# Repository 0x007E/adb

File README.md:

# `ADB` - Analog Development Board

The `ADB` is a board with an [LM358](#additional-information) or any other 2-channel operational amplifier that meets the pin requirements. The board itself can be driven from `0 to 30V` or `+/-15V`. The board offers the possibility to create standard `OPA` circuits with `THT` resistors/capacitors and inductors or any other external circuit.

| Experience | Level |
|:------------|:-----:|
| Soldering   |  |

# Downloads

| Type      | File               | Description              |
|:---------:|:------------------:|:-------------------------|
| Schematic | [pdf](https://github.com/0x007E/adb/releases/latest/download/schematic.pdf) / [cadlab](https://cadlab.io/project/29896/main/files) | Schematic files |
| Board | [pdf](https://github.com/0x007E/adb/releases/latest/download/pcb.pdf) / [cadlab](https://cadlab.io/project/29896/main/files) | Board file |
| Drill | [pdf](https://github.com/0x007E/adb/releases/latest/download/drill.pdf) | Drill file |
| PCB | [zip](https://github.com/0x007E/adb/releases/latest/download/kicad.zip) / [tar](https://github.com/0x007E/adb/releases/latest/download/kicad.tar.gz) |  	KiCAD/Gerber/BoM/Drill files |
| Mechanical | [zip](https://github.com/0x007E/adb/releases/latest/download/freecad.zip) / [tar](https://github.com/0x007E/adb/releases/latest/download/freecad.tar.gz) | FreeCAD/Housing and exported step/stl files |

# Hardware

The pcb is created with `KiCAD`. All files are built with `github actions` so that they are ready for a production environment.

## PCB

The circuit board is populated on both sides (Top, Bottom). The best way for soldering the `SMD` components is within a vapor phase soldering system and for the `THT` components with a standard soldering system.

### Top Layer

### Bottom Layer

# Additional Information

| Type       | Link               | Description              |
|:----------:|:------------------:|:-------------------------|
| LM358 | [pdf](https://www.onsemi.com/download/data-sheet/pdf/lm358-d.pdf) | Dual operational amplifier |

---

R. GAECHTER

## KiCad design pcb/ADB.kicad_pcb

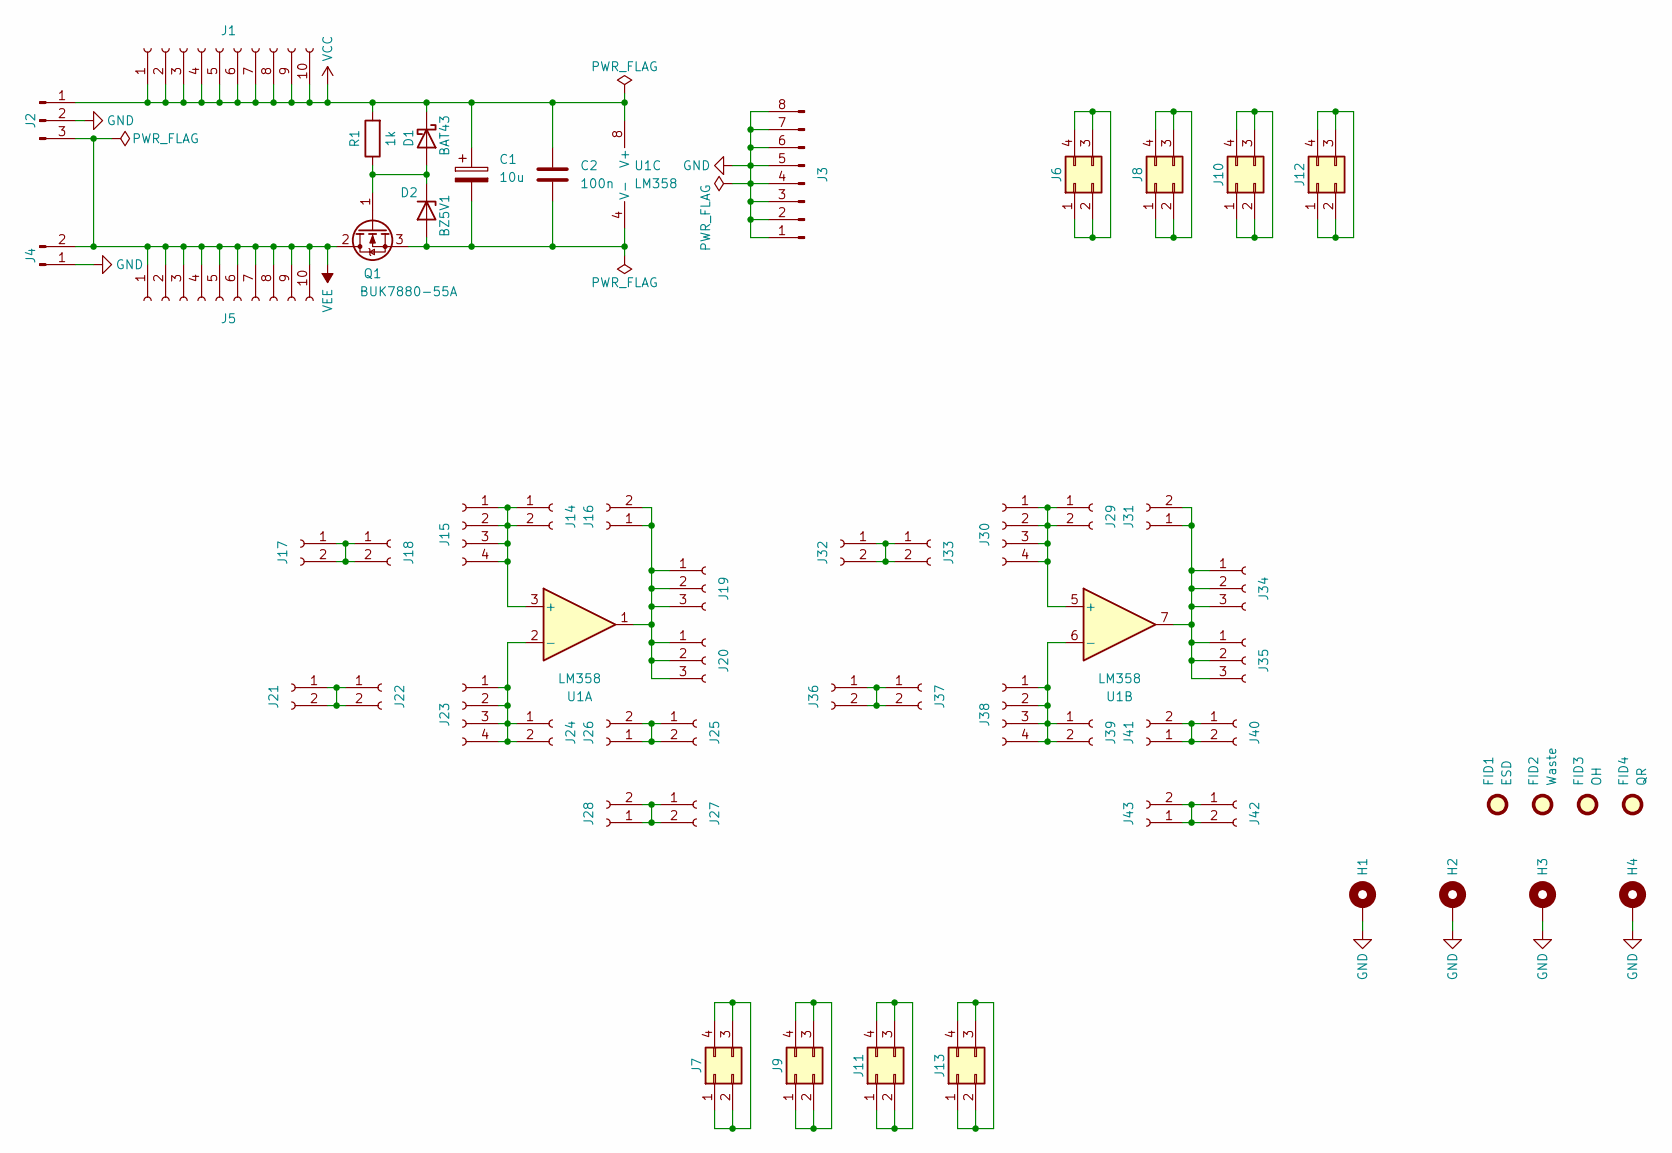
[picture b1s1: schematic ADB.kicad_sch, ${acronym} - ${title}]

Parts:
C1: 10u; CP_Radial_D6.3mm_P2.50mm
C2: 100n; C_1206_3216Metric
D1: BAT43; D_MiniMELF
D2: BZ5V1; D_MiniMELF
FID1: ESD; ESD-Logo_6.6x6mm_SilkScreen
FID2: Waste; WEEE-Logo_4.2x6mm_SilkScreen
FID3: OH; OSHW-Logo_5.7x6mm_SilkScreen
FID4: QR; QR_0x007e
H1, H2, H3, H4: MountingHole_Pad; MountingHole_3.2mm_M3_Pad
J1, J5: Conn_01x10_Socket; PinSocket_1x10_P2.54mm_Vertical
J2: Conn_01x03_Pin; PinHeader_1x03_P2.54mm_Vertical
J3: Conn_01x08_Pin; PinHeader_1x08_P2.54mm_Vertical
J4: Conn_01x02_Pin; PinHeader_1x02_P2.54mm_Vertical
J6, J7, J8, J9, J10, J11, J12, J13: Conn_02x02_Counter_Clockwise; PinSocket_2x02_P2.54mm_Vertical
J14, J16, J17, J18, J21, J22, J24, J25, J26, J27, J28, J29, J31, J32, J33, J36, J37, J39, J40, J41, J42, J43: Conn_01x02_Socket; PinSocket_1x02_P2.54mm_Vertical
J15, J23, J30, J38: Conn_01x04_Socket; PinSocket_1x04_P2.54mm_Vertical
J19, J20, J34, J35: Conn_01x03_Socket; PinSocket_1x03_P2.54mm_Vertical
Q1: BUK7880-55A; SOT-223-3_TabPin2
R1: 1k; R_1206_3216Metric
U1: LM358; SOIC-8_3.9x4.9mm_P1.27mm

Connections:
GND: H1.1, H2.1, H3.1, H4.1, J2.2, J3.1, J3.2, J3.3, J3.4, J3.5, J3.6, J3.7, J3.8, J4.1
unnamed: D1.2 (A), D2.1 (K), Q1.1 (G), R1.1
unnamed: C1.2, C2.2, D2.2 (A), Q1.3 (S), U1.4 (V-)
unnamed: J6.1, J6.2, J6.3, J6.4
unnamed: J7.1, J7.2, J7.3, J7.4
unnamed: J8.1, J8.2, J8.3, J8.4
unnamed: J9.1, J9.2, J9.3, J9.4
unnamed: J10.1, J10.2, J10.3, J10.4
unnamed: J11.1, J11.2, J11.3, J11.4
unnamed: J12.1, J12.2, J12.3, J12.4
unnamed: J13.1, J13.2, J13.3, J13.4
unnamed: J14.1, J14.2, J15.1, J15.2, J15.3, J15.4, U1.3 (+)
unnamed: J16.1, J16.2, J19.1, J19.2, J19.3, J20.1, J20.2, J20.3, U1.1
unnamed: J17.1, J17.2, J18.1, J18.2
unnamed: J21.1, J21.2, J22.1, J22.2
unnamed: J23.1, J23.2, J23.3, J23.4, J24.1, J24.2, U1.2 (-)
unnamed: J25.1, J25.2, J26.1, J26.2
unnamed: J27.1, J27.2, J28.1, J28.2
unnamed: J29.1, J29.2, J30.1, J30.2, J30.3, J30.4, U1.5 (+)
unnamed: J31.1, J31.2, J34.1, J34.2, J34.3, J35.1, J35.2, J35.3, U1.7
unnamed: J32.1, J32.2, J33.1, J33.2
unnamed: J36.1, J36.2, J37.1, J37.2
unnamed: J38.1, J38.2, J38.3, J38.4, J39.1, J39.2, U1.6 (-)
unnamed: J40.1, J40.2, J41.1, J41.2
unnamed: J42.1, J42.2, J43.1, J43.2
VCC: C1.1, C2.1, D1.1 (K), J1.1, J1.2, J1.3, J1.4, J1.5, J1.6, J1.7, J1.8, J1.9, J1.10, J2.1, R1.2, U1.8 (V+)
VEE: J2.3, J4.2, J5.1, J5.2, J5.3, J5.4, J5.5, J5.6, J5.7, J5.8, J5.9, J5.10, Q1.2 (D)

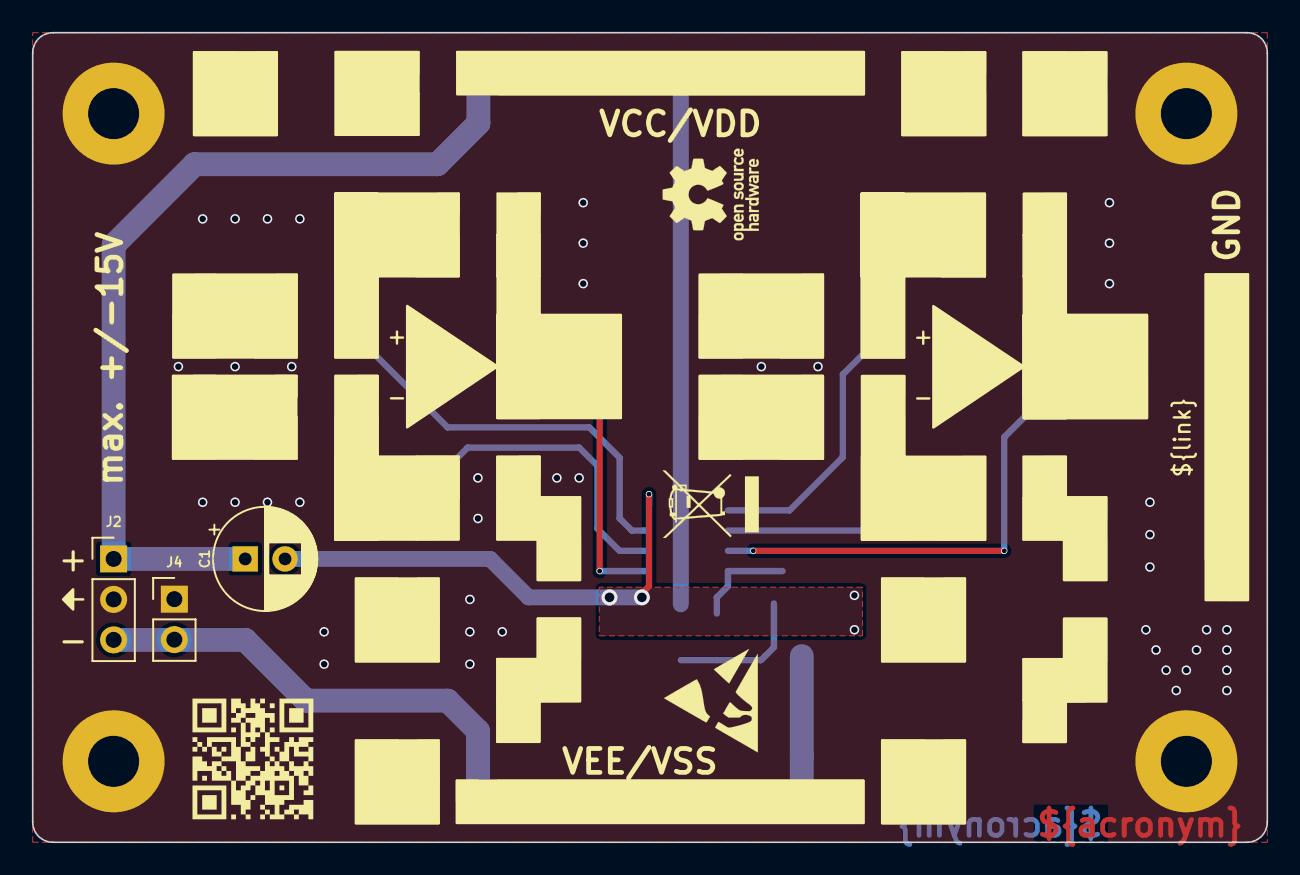
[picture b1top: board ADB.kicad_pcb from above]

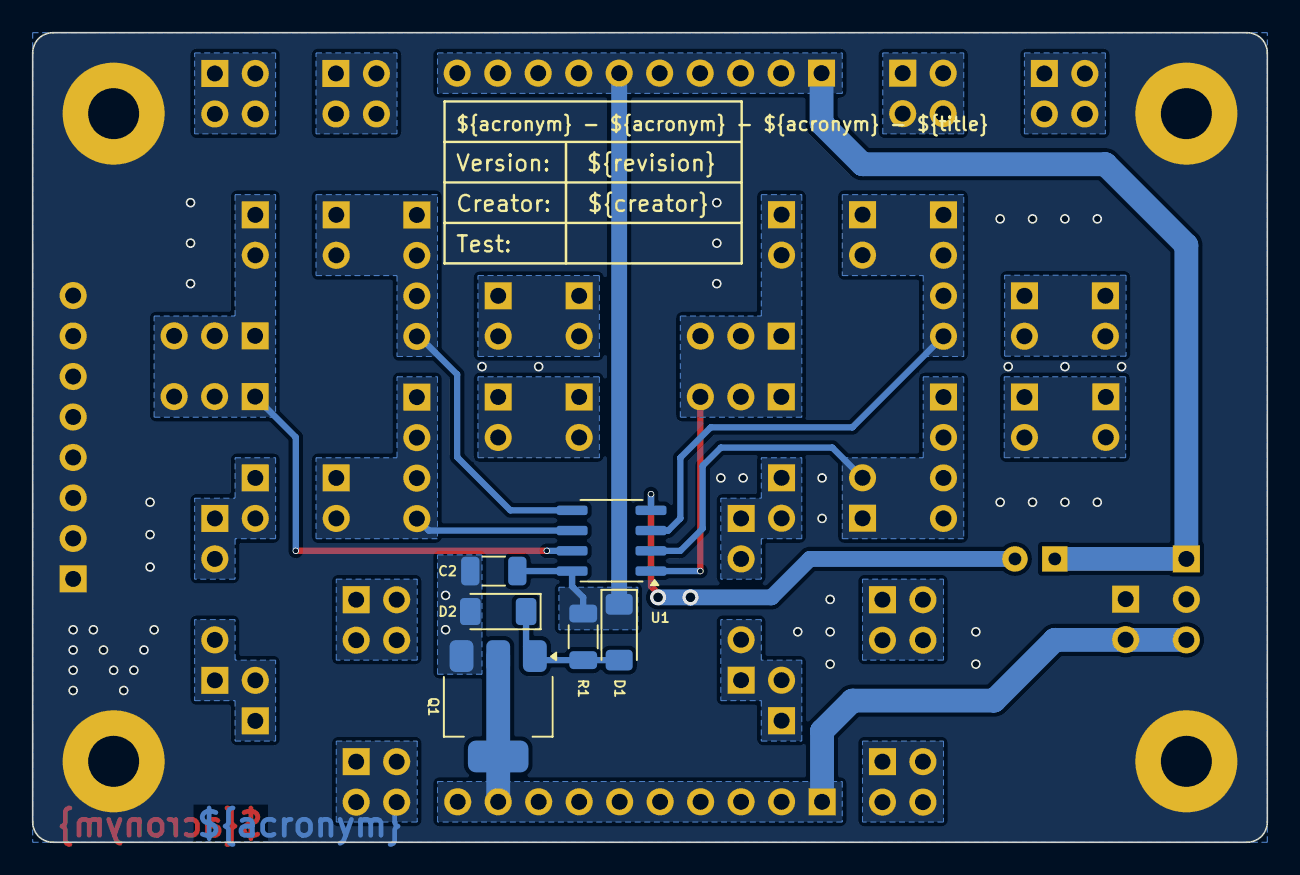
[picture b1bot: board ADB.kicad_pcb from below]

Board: 2 copper layers, 77.5 x 50.8 mm, 58 parts (6 on the bottom side), 27 nets.

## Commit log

2026-02-06 Add pcb layout
2026-02-06 Add README.md
2026-02-06 Add build pipeline
2026-02-06 Add release pipeline
2026-02-06 Add more vias
2026-02-06 Fix negative voltage descriptors
2026-02-07 Add gh-link
2026-02-08 Reposition of U1 on silkscreen
2026-03-09 Remove invalid text
2026-03-22 Adapt edge cuts and dimensioning
2026-03-22 Add FreeCAD export
2026-03-23 Add FreeCAD modification
2026-03-23 Add mechanical download link
2026-03-23 Remove unnecessary file upload
2026-05-08 Add reverse polarity protection
2026-05-09 Remove isolated copper filter
2026-05-09 Increase power trace width
2026-05-11 Optimize fabrication layer
2026-05-12 Adapt description

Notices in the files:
README.md:
License CC By-NC-SA
parts and their libraries:
license: CC BY-NC-SA 4.0
